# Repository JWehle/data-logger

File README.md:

# data-logger
A modular board for logging analog measurements.

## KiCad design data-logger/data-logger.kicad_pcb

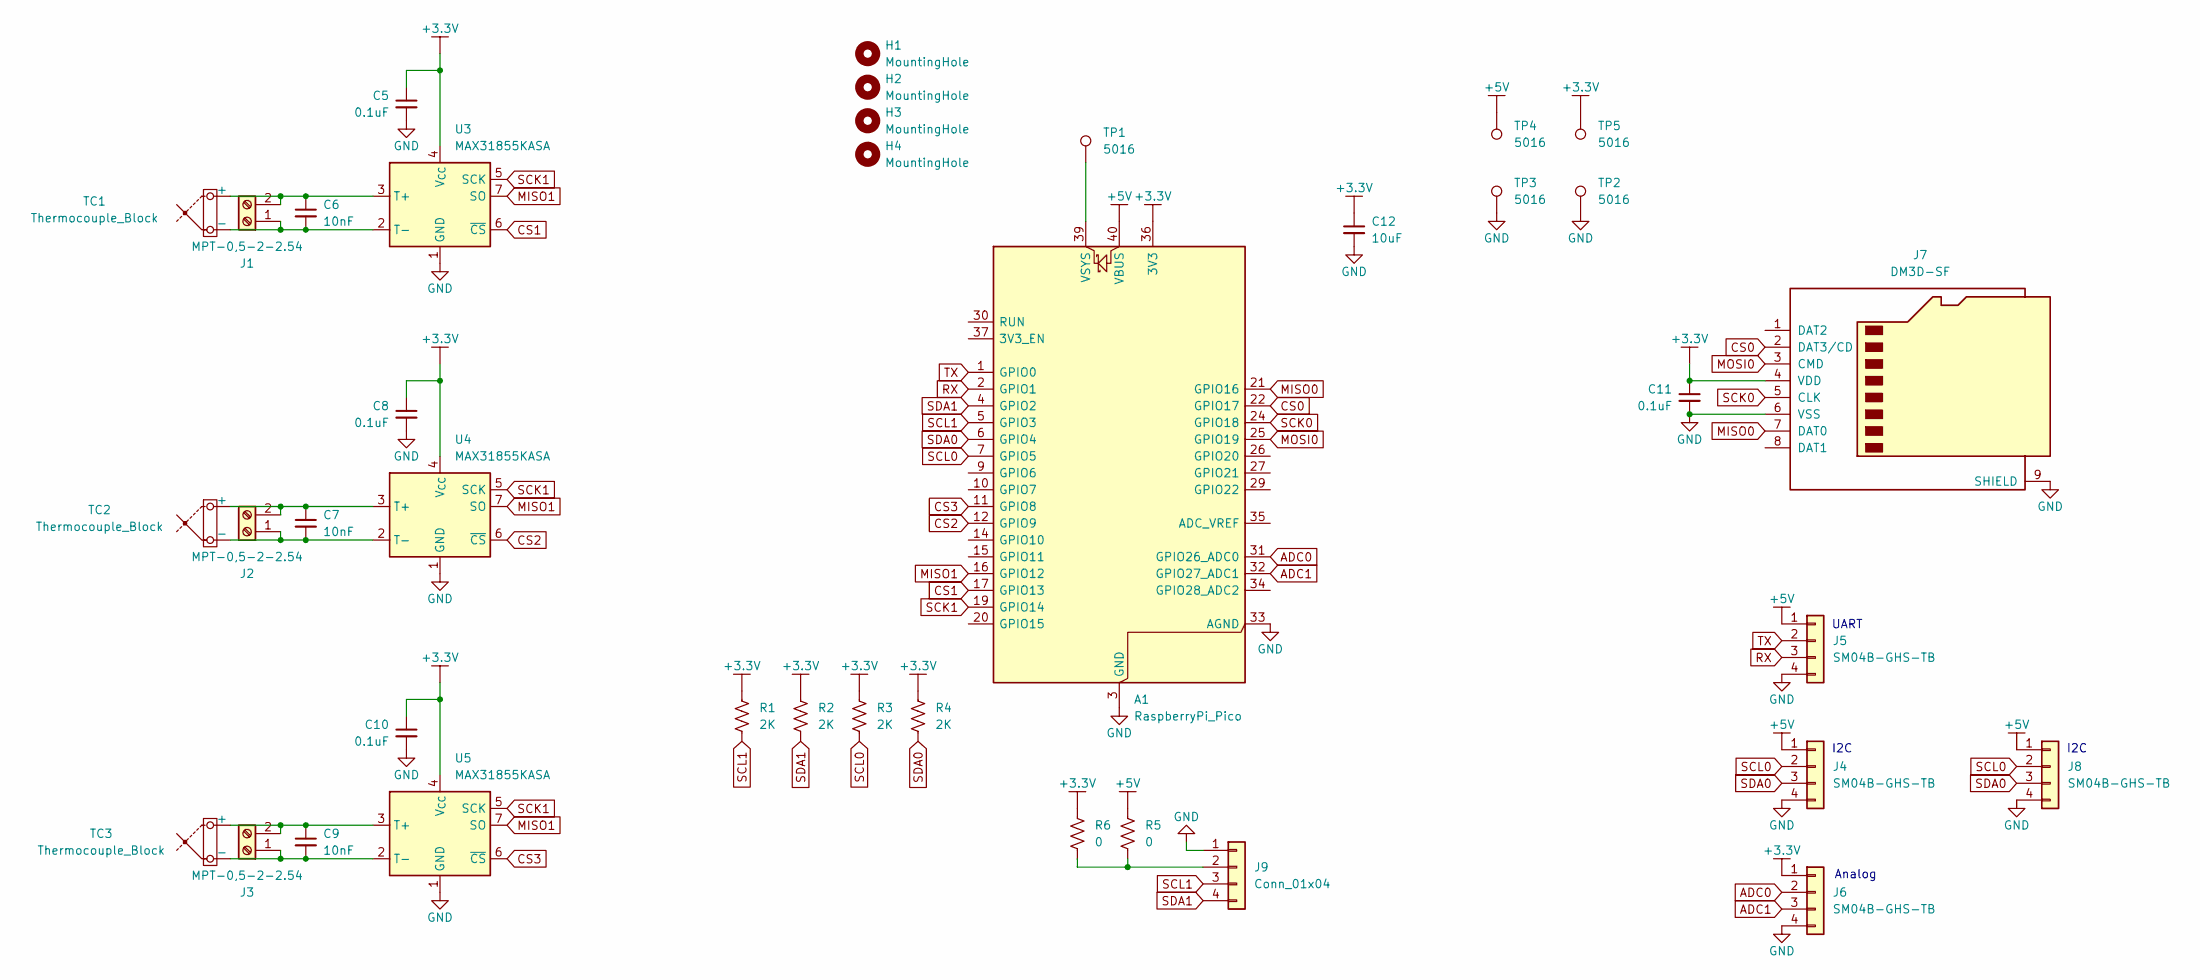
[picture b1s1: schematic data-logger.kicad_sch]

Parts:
A1: RaspberryPi_Pico; RaspberryPi_Pico_Common_Unspecified
C5, C8, C10, C11: 0.1uF; C_0603_1608Metric
C6, C7, C9: 10nF; C_0603_1608Metric
C12: 10uF; C_0603_1608Metric
H1, H2, H3, H4: MountingHole; MountingHole_3.2mm_M3
J1, J2, J3: MPT-0,5-2-2.54; TerminalBlock_Phoenix_MPT-0,5-2-2.54_1x02_P2.54mm_Horizontal
J4, J5, J6, J8: SM04B-GHS-TB; JST_GH_SM04B-GHS-TB_1x04-1MP_P1.25mm_Horizontal
J7: DM3D-SF; microSD_HC_Hirose_DM3D-SF
J9: Conn_01x04; PinSocket_1x04_P2.54mm_Vertical
R1, R2, R3, R4: 2K; R_0603_1608Metric_Pad0.98x0.95mm_HandSolder
R5, R6: 0; R_0603_1608Metric_Pad0.98x0.95mm_HandSolder
TC1, TC2, TC3: Thermocouple_Block
TP1, TP2, TP3, TP4, TP5: 5016; TestPoint_Keystone_5016_Vias
U3, U4, U5: MAX31855KASA; SOIC-8_3.9x4.9mm_P1.27mm

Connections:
+3.3V: A1.36 (3V3), C5.1, C8.1, C10.1, C11.1, C12.1, J6.1, J7.4 (VDD), R1.1, R2.1, R3.1, R4.1, R6.1, TP5.1, U3.4 (V_{CC}), U4.4 (V_{CC}), U5.4 (V_{CC})
+5V: A1.40 (VBUS), J4.1, J5.1, J8.1, R5.1, TP4.1
ADC0: A1.31 (GPIO26_ADC0), J6.2
ADC1: A1.32 (GPIO27_ADC1), J6.3
CS0: A1.22 (GPIO17), J7.2 (DAT3/CD)
CS1: A1.17 (GPIO13), U3.6 (~CS)
CS2: A1.12 (GPIO9), U4.6 (~CS)
CS3: A1.11 (GPIO8), U5.6 (~CS)
GND: A1.3 (GND), A1.8 (GND), A1.13 (GND), A1.18 (GND), A1.23 (GND), A1.28 (GND), A1.33 (AGND), A1.38 (GND), C5.2, C8.2, C10.2, C11.2, C12.2, J4.4, J5.4, J6.4, J7.6 (VSS), J7.9 (SHIELD), J8.4, J9.1, TP2.1, TP3.1, U3.1 (GND), U4.1 (GND), U5.1 (GND)
MISO0: A1.21 (GPIO16), J7.7 (DAT0)
MISO1: A1.16 (GPIO12), U3.7 (SO), U4.7 (SO), U5.7 (SO)
MOSI0: A1.25 (GPIO19), J7.3 (CMD)
unnamed: A1.39 (VSYS), TP1.1
unnamed: C6.2, J1.1, TC1.2 (-), U3.2 (T-)
unnamed: C6.1, J1.2, TC1.1 (+), U3.3 (T+)
unnamed: C7.2, J2.1, TC2.2 (-), U4.2 (T-)
unnamed: C7.1, J2.2, TC2.1 (+), U4.3 (T+)
unnamed: C9.2, J3.1, TC3.2 (-), U5.2 (T-)
unnamed: C9.1, J3.2, TC3.1 (+), U5.3 (T+)
unnamed: J9.2, R5.2, R6.2
RX: A1.2 (GPIO1), J5.3
SCK0: A1.24 (GPIO18), J7.5 (CLK)
SCK1: A1.19 (GPIO14), U3.5 (SCK), U4.5 (SCK), U5.5 (SCK)
SCL0: A1.7 (GPIO5), J4.2, J8.2, R3.2
SCL1: A1.5 (GPIO3), J9.3, R1.2
SDA0: A1.6 (GPIO4), J4.3, J8.3, R4.2
SDA1: A1.4 (GPIO2), J9.4, R2.2
TX: A1.1 (GPIO0), J5.2

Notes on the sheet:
I2C
Analog
UART

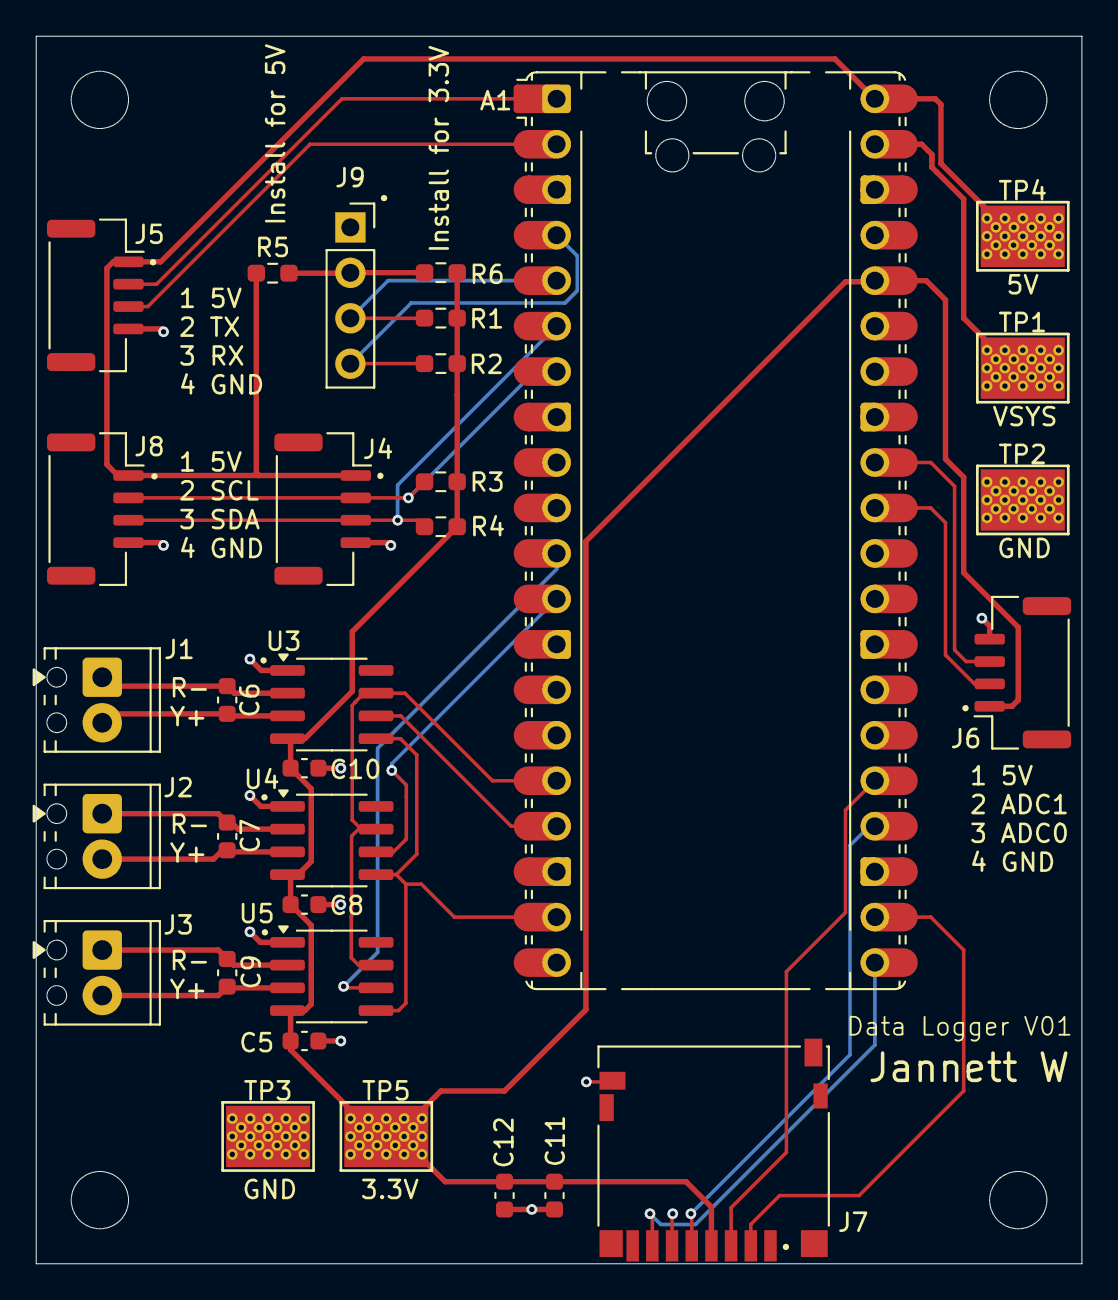
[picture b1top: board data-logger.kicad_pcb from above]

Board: 2 copper layers, 58.4 x 68.6 mm, 36 parts (0 on the bottom side), 28 nets.

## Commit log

2025-03-09 changed architecture in schematic
2025-05-18 schematic
2025-06-15 layout
2025-06-15 layouts
2025-06-15 finished
2025-08-18 edits
